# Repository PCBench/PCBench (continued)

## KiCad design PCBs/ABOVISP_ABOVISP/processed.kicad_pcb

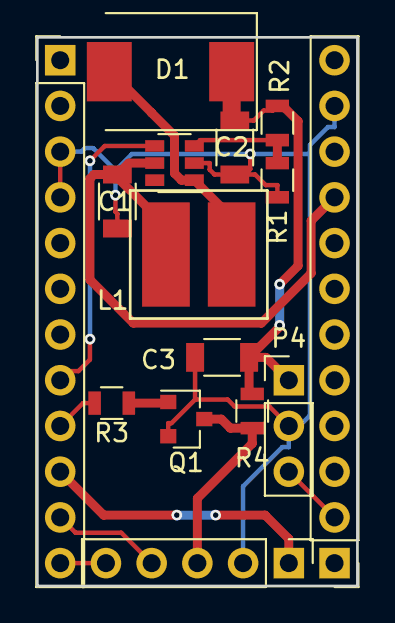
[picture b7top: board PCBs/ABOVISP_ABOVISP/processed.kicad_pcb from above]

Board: 2 copper layers, 17.8 x 30.5 mm, 15 parts (0 on the bottom side), 13 nets.

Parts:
C1, C2: 22uF; C_1206
C3: 10uF; C_1206
D1: SS34; D_SMC_Standard
L1: 4.7uH; SMD_Inductor_CD54
P1: CONN_01X05; Socket_Strip_Straight_1x05_Pitch2.54mm
P2, P3: CONN_01X12; Socket_Strip_Straight_1x12_Pitch2.54mm
P4: CONN_01X03; Socket_Strip_Straight_1x03_Pitch2.54mm
Q1: MMBT3904; SOT-23
R1: 2.2K; R_0805
R2: 33K; R_0805
R3: 1K; R_0805
R4: 10K; R_0805
U1: MT3608; SOT-23-6

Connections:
9V: C2.1, C3.1, D1.1, P4.1, R2.2, R4.1
+5V: C1.1, L1.1, P3.9, U1.5
BOOST_EN: P2.8, U1.4
GND: C1.2, C2.2, C3.2, P1.2, P2.3, P2.4, P3.11, P4.2, Q1.2, R1.2, U1.2
GPIO_16: P3.2, P4.3
unnamed: D1.2, L1.2, U1.1
unnamed: Q1.1, R3.1
unnamed: R1.1, R2.1, U1.3
PROG_SCK: P1.4, P2.11
PROG_SDA: P1.5, P2.12
PROG_VCC: P1.1, P2.10
PROG_VPP: P1.3, Q1.3, R4.2
TRIG_VPP: P2.9, R3.2

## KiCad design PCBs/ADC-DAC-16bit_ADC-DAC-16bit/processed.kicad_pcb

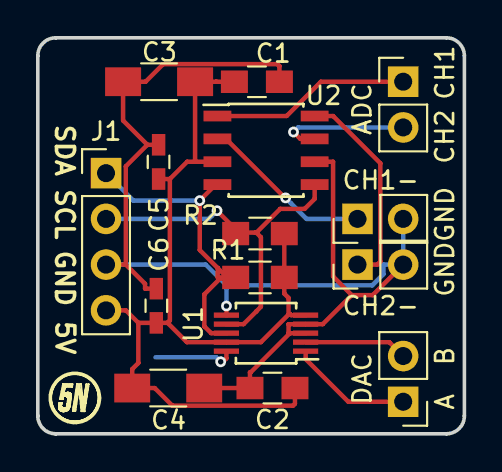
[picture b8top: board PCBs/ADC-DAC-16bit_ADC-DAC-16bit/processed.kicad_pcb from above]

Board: 2 copper layers, 23.7 x 22.0 mm, 16 parts (1 on the bottom side), 11 nets.

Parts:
C1, C2: 100n; C_0805_HandSoldering
C3, C4: 10u; C_1206_HandSoldering
C5, C6: 100n; C_0603_HandSoldering
J1: CON; Pin_Header_Straight_1x04_Pitch2.54mm
J2: DAC; Pin_Header_Straight_1x02_Pitch2.54mm
J3: ADC; Pin_Header_Straight_1x02_Pitch2.54mm
J4: CH1-; Pin_Header_Straight_1x02_Pitch2.54mm
J5: CH2-; Pin_Header_Straight_1x02_Pitch2.54mm
R1, R2: 4K7; R_0805_HandSoldering
TP1: DAC Vref; Measurement_Point_Round-SMD-Pad_Small
U1: AD5667R; MSOP-10_3x3mm_Pitch0.5mm
U2: MCP3426; SOIC-8_3.9x4.9mm_Pitch1.27mm

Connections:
+5V: C1.1, C2.1, C3.1, C4.1, C5.1, C6.1, J1.4, R1.1, R2.1, U1.5, U1.9, U2.3
GND: C1.2, C2.2, C3.2, C4.2, C5.2, C6.2, J1.3, J4.2, J5.2, U1.3, U1.4, U1.6, U2.6
unnamed: J1.1, R1.2, U1.8, U2.4
unnamed: J1.2, R2.2, U1.7, U2.5
unnamed: J2.1, U1.1
unnamed: J2.2, U1.2
unnamed: J3.1, U2.1
unnamed: J3.2, U2.7
unnamed: J4.1, U2.2
unnamed: J5.1, U2.8
unnamed: TP1.1, U1.10
